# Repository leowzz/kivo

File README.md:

# Kivo

把实体按键变成电脑里的文字、快捷键和自动化动作。

[下载最新版本](https://github.com/leowzz/kivo/releases/latest) · [快速上手](#快速上手) · [刷入固件](#刷入固件) · [本地开发](#本地开发)

Kivo 包含两个独立的 Tauri 桌面入口：日常使用的 **Kivo APP**，以及配置产品、硬件和固件的 **Kivo Studio**。APP 从设备读取产品定义，负责按键动作；Studio 负责生成产品固件并检查 GPIO 电平。

## 能做什么

- **执行桌面动作**：按顺序组合文字粘贴、快捷键、等待、媒体控制，以及打开应用、网址、文件或文件夹。
- **配置触发方式**：为按下、松开、长按和双击分别配置动作，并调整长按、双击的判定时间。
- **配置产品硬件**：Studio 编辑按键布局、直连 GPIO、触点矩阵、功能开关和显示模块。
- **测试 GPIO 电平**：Studio 实时展示板卡允许使用的 GPIO 高低电平，支持 YD-ESP32-S3 和 YD-RP2040。
- **管理多台设备**：每台产品设备独立选择动作配置；相同产品版本的设备可以共享配置，也可以复制一份单独修改。
- **兼容旧版配置**：通用固件仍可使用包含布局、动作和多个 Hardware Profile 的 Device Profile。
- **功能开关门控**：Hardware Profile 可把一个 GPIO 开关绑定到若干按钮；开关断开时，这些按钮不会执行动作。
- **编辑按键动作**：APP 展示设备键盘，支持动作列表、自动保存、撤销和重做。
- **迁移与恢复**：导入旧版设备配置，备份和恢复产品设备的动作配置及其选择关系；仍兼容恢复旧版全量备份。

## 快速上手

1. 从 [Releases](https://github.com/leowzz/kivo/releases/latest) 下载 macOS 安装包或 Windows x64 安装程序。
2. 已刷入产品固件的设备直接连接 USB 即可。裸板或需要更换固件的设备，先按[刷入固件](#刷入固件)选择产品固件或通用固件。通过身份与协议校验后，Kivo 会自动登记设备。
3. 产品固件会直接提供按键布局和硬件定义。在 APP 的“我的键盘”中选中设备，再选择或新建动作配置。
4. 点击按键，为不同触发方式编辑动作。修改自动保存，提供撤销和重做；修改共享配置会影响所有正在使用它的设备，需要独立设置时先复制配置。
5. 改接线、布局或显示模块时，使用 Studio 修改产品定义并重新构建固件。
6. 通用固件仍可使用已有 Device Profile：通过“添加键盘”选择兼容配置，或从“数据与备份”导入旧配置。

产品设备会按 Product Version ID 选择已有或默认动作配置。通用固件设备在获得有效 Runtime Assignment 前不会执行动作；编辑中的 Device Profile 不会自动替换其他设备正在使用的配置。

动作库中的“打开应用”可选择应用、拖入应用或快捷方式，也可填写完整路径：macOS 支持 `.app`，Windows 支持 `.exe`、`.com` 和 `.lnk`。“打开网址”使用默认浏览器，支持 HTTP 和 HTTPS，未填写协议时自动使用 HTTPS。选择目标并保存后，这些动作会按配置顺序执行。

APP 的“设置 → 应用更新”和 Studio 的“应用更新”可手动检查新版。桌面应用也会在启动及重新回到前台时检查更新；发现新版后，点击“更新并重启”即可下载、验证并安装更新。更新应用前请先保存修改并完成设备操作。应用更新不会刷写设备固件。

“数据与备份”中的“备份设备行为”导出产品动作配置与设备选择关系，不包含固件、布局、接线、统计数据或旧版 Device Profile，不能当作整个工作区的全量备份。设备 Flash 的备份与恢复在 Studio 的工具台完成。

## 刷入固件

先区分两类固件：

- **产品固件**：由 Studio 根据 `products/<product-version-id>/product.yaml` 构建，内嵌布局和接线，APP 可自动识别。使用已有产品时应选择对应产品产物；构建与刷写步骤见[本地开发](#本地开发)和[固件](#固件)。
- **通用固件**：Release 中按板卡命名的文件，不含具体产品定义，需要在 APP 中分配兼容的旧版 Device Profile。不要把它当作某个产品的预配置固件。

从 [Releases](https://github.com/leowzz/kivo/releases/latest) 下载的通用固件命名如下：

| 板卡 | 选择这个文件 |
|---|---|
| YD-ESP32-S3 | `kivo-vX.Y.Z-esp32s3.bin` |
| YD-RP2040 | `kivo-vX.Y.Z-rp2040.uf2` |

### YD-RP2040：拖入文件管理器

1. 让板卡进入 BOOTSEL 模式：
   - 板卡尚未连接时，按住 **BOOT**，插入 USB；看到 `RPI-RP2` 磁盘后松开 **BOOT**。
   - 板卡已经连接时，按住 **BOOT**，短按一次 **RESET**，然后松开 **BOOT**。
2. 在 Finder 或文件资源管理器中打开 `RPI-RP2`。
3. 把 `kivo-vX.Y.Z-rp2040.uf2` 拖进磁盘。复制完成后磁盘会自动退出，板卡会运行 Kivo 固件。

### ESP32-S3：在浏览器中选择固件

ESP32-S3 的下载模式不会显示成磁盘。请使用 Chrome 或 Edge：

1. 下载 `kivo-vX.Y.Z-esp32s3.bin`，打开 Espressif 官方的 [ESP Tool](https://espressif.github.io/esptool-js/)。
2. 按住板卡的 **BOOT**，短按一次 **RESET/RST**，然后松开 **BOOT**。
3. 点击 **Connect**，选择刚出现的 ESP32-S3 串口。
4. 点击 **Add File**，地址填写 `0x0`，选择下载的 `.bin` 文件。
5. 点击 **Program**。完成后短按一次 **RESET/RST**，板卡会运行 Kivo 固件。

只使用上表中与板卡匹配的文件。刷写完成后保持 USB 连接，Kivo 会自动检测设备。

## 配置怎样组合

| 概念 | 负责什么 |
|---|---|
| Product Definition | Studio 编辑并嵌入固件的产品身份、布局和硬件定义 |
| Product Configuration Profile | APP 编辑的触发设置与动作；同一 Product Version ID 的设备可以共享，修改影响所有选用它的设备 |
| Device Profile | 通用固件的旧版兼容格式，包含布局、动作及一个或多个 Hardware Profile |
| Hardware Profile | 面向具体板卡的接线拓扑、输入绑定和去抖设置 |
| Device | 一台有稳定硬件序列号的实体控制器；USB 端口不是设备身份 |
| Runtime Assignment | 把一个 Device Profile 和兼容的 Hardware Profile 分配给一台 Device |
| Editor Profile | 当前正在界面中编辑的 Device Profile，不影响其他设备运行 |

功能开关属于 Hardware Profile 的输入源，不会出现在按键布局中。配置时只需选择开关 GPIO 和受影响的按钮。开关闭合时启用按钮；断开或 helper 尚未确认开关状态时屏蔽按钮。被屏蔽的按键不会计入动作统计，正在执行的动作会完整结束。

## 硬件产品命名

Kivo 实体产品使用 `<product-family>-<controller>-k<key-count>[-<capability>...]-r<hardware-revision>`
形式的 Product Version ID。产品能力变体和 PCB 修订彼此独立，软件发布版本、固件
版本、生产批次和单台设备序列号不进入该 ID。

仓库目前包含 WBRP-K18 的 r02、r03 产品定义：RP2040、18 个独立实体按键、显示屏，
以及可旋转、可按压的编码器。例如：

```text
kivo-workbench-rp-k18-disp-encp-r03
```

其中 `rp` 表示 RP2040，`k18` 不包含编码器按压，`encp` 表示编码器同时支持旋转和按压。
当前这两份产品定义不声明麦克风能力。产品 YAML 的存在不代表对应 PCB 已可投产；
[`hardware/workbench-r03/`](hardware/workbench-r03/README.md) 仍标记为未布线的设计草稿。
完整字段定义、token 顺序和升级规则见[产品版本 ID 命名规范](docs/product-version-id-naming.md)。

## 支持的控制器

| 板卡 | Controller Family | 运行时 USB | 固件环境 | 上传命令 |
|---|---|---|---|---|
| YD-ESP32-S3 | ESP32-S3 | `303a:4002` | `esp32s3` | `make upload-esp32s3` |
| YD-RP2040 | RP2040 | `2e8a:102e` | `rp2040` | `make upload-rp2040` |

YD-RP2040 的 UF2 bootloader USB 标识为 `2e8a:0003`。Kivo 会先校验 USB 身份，再通过 `HELLO` 协议确认板卡和固件；不受该 Board Profile 支持的 GPIO 会被拒绝。

YD-RP2040 的 Hardware Profile 支持两种地址为 `0x3C` 的 OLED：原有 SSD1306 128x32 模块占用 SDA/SCL 两个 GPIO；`sh1106-1.3-128x64-ec11` 模块使用 SH1106 128x64 屏，并带 EC11 旋转、EC11 按压、确认和返回，共占用七个 GPIO。OLED 和控制面板占用的 GPIO 不会再分配给按键输入。

## Codex 状态屏

启用 OLED 的设备会显示本机 Codex 任务的低干扰状态：汇总画面为 `CODEX <N> RUN`，需要操作时显示 `NEEDS INPUT` 或 `APPROVAL NEEDED`，响应生成后短暂显示 `RESPONSE READY`，数据源不可用时显示 `CODEX OFFLINE`。Codex 数据源异常不会停止 Kivo 的按键 Runtime。

状态屏使用任务身份、工作目录和状态/生命周期信号，不展示对话正文、推理、工具内容或最终回复。SSD1306 使用 `ssd1306_128x32` 面板和 128x32 渲染器；SH1106 使用 `sh1106_128x64` 面板和 128x64 渲染器。当前仓库的运行固件握手为 `HELLO 15`。两种屏均固定为 rotation 0，互不迁移。

带编码器的屏幕还提供 RunCat：按压编码器进入菜单，选择 `RUNCAT`，旋转编码器依次切换经典跑猫、兔子、柯基、飞鸟、奔马、恐龙、转子发动机、擒纵机构、双曲柄和 UFO 吸牛，共 10 套动画。素材来自 [Runner Gallery](https://github.com/runcat-dev/RunnerGallery)，保留各套完整的 5–24 帧循环；动画铺满屏幕高度，CPU 指标位于最右侧，不显示标题。动画选择会保存，按压编码器或返回键回到菜单，从 `LIVE VIEW` 恢复任务状态屏。电脑 CPU 使用率越高，动画播放越快；Kivo 未连接或 CPU 数据超过 3 秒未更新时显示 `CPU --`，动画以低速播放。此功能需要配套更新 Kivo 和运行固件。素材来源与许可证见 [assets/runcat/NOTICE.md](assets/runcat/NOTICE.md)。

带编码器的 r02 工作站使用产品固件：先运行 `make build-product PRODUCT=kivo-workbench-rp-k18-disp-encp-r02`，再用 `make upload-prod` 选择刚构建的 r02 固件。`make upload` 上传通用固件，不包含产品的屏幕和编码器接线；刷入后无法独立使用该模块的菜单。

刷入固件后仍需分别在实体 SSD1306 和 SH1106 上检查文字与状态切换，并在 SH1106 模块上检查旋钮方向、按压、确认和返回。自动测试和固件构建不能替代物理屏幕与输入验收。

两种控制器共享按键扫描、去抖、协议和运行状态机，各自保留 USB/HID 平台适配。多台 ESP32-S3 与 YD-RP2040 可以同时在线：产品设备使用各自选择的产品动作配置，通用固件设备使用各自的 Runtime Assignment。

## 本地开发

需要：

- Node.js `>=24.12.0 <25` 与 npm `>=11.0.0 <12`；`.nvmrc` 和
  `packageManager` 记录 CI 使用的参考版本
- Rust stable 和 Tauri 2 所需的系统构建依赖
- Python `3.13`、[`uv`](https://docs.astral.sh/uv/) 与 PlatformIO
- macOS 或 Windows；发行工作流构建 macOS universal DMG 和 Windows x64 NSIS 安装程序
- 使用 `make` 目标需要 GNU Make；Windows 还需可用的 Bash。Git for Windows 可以提供 Bash，但 GNU Make 需要单独安装

```bash
git clone https://github.com/leowzz/kivo.git
cd kivo
cp .env.example .env

nvm install
nvm use
uv sync
npm ci
make client
```

`.env` 会被有意忽略，且只包含 `version=vX.Y.Z`。它为本地固件构建和 `make release` 提供仓库版本。

### 两个桌面入口

| 命令 | 用途 |
|---|---|
| `make client` | 启动 Kivo APP，管理设备和按键动作 |
| `make studio` | 启动 Kivo Studio，编辑产品定义、构建固件、测试 GPIO |
| `make helper-build-app` | 单独打包 APP |
| `make helper-build-studio` | 单独打包 Studio |
| `make helper-build` | 打包两个入口 |
| `make test` | 前端、两个 Rust 入口、固件逻辑与构建流程验证 |

浏览器开发使用 `npm run dev` 和 `npm run dev:studio`，默认端口分别为 1420 和 1421。
APP 的 `/?preview` 仅在开发环境提供交互预览；真实串口和文件操作需要 Tauri。

Studio 使用独立的应用标识和配置目录，不会启动 APP 的设备运行服务。产品定义编辑可以与 APP 同时运行；GPIO 测试需要独占目标串口，测试前退出 APP 或其他串口工具。

安装版 Studio 首次使用时需要选择包含 `products/` 和固件源码的 Kivo 仓库；构建、备份和刷写还依赖本机的 `uv`、PlatformIO 等工具链，安装桌面包本身并不等于已配置固件开发环境。

已保存产品的 Capabilities 可直接修改；能力变化会同步更新产品 ID，保存时创建对应的新变体。
构建完成后，日志面板提供“复制输出路径”和“刷入固件”。后者直接使用本次构建文件，筛选匹配板卡的设备，校验文件后确认覆盖；未保存的修改需要先保存并重新构建。

### 工具台

Studio 的“工具台”集中提供刷新设备列表、备份固件、刷入固件文件和刷入测试固件四项操作，并可查看 GPIO 高低电平。

- **刷新设备列表**：重新枚举受支持的板卡，操作按序列号定位所选物理设备。
- **备份固件**：读取整片 Flash，RP2040 保存为 UF2，ESP32-S3 保存为 BIN；同时保存 `.backup.json` 校验记录。读取失败不会覆盖已有备份。
- **刷入固件文件**：选择 RP2040 UF2 或 ESP32-S3 完整 Flash / factory BIN，检查芯片、文件结构和 SHA-256 后确认刷写。支持恢复备份；若文件附带产品 `manifest.json`，额外校验清单和刷写后的产品、构建身份。ESP32-S3 写入地址固定为 `0x0`，拒绝仅含应用、应写入 `0x10000` 的 BIN。
- **刷入测试固件**：自动构建所选板卡的临时 I/O 固件，首次刷入前备份原固件，完成后开始采样。测试固件不含产品接线、按键动作、矩阵扫描或显示驱动；安全 GPIO 默认上拉输入，可切换浮空或下拉，串口断开时回到上拉输入。Studio 每次开始测试时也会先为临时固件启用上拉，兼容默认浮空的旧测试固件。

原固件备份位于 `output/firmware-backups/<board>/<device>/`，工具台显示具体路径。备份按设备持久保存，重复刷测试固件会复用原备份，不会把测试固件覆盖到原备份。测试完成后停止采样，点击“刷入固件文件”，文件选择器会默认定位到原备份。恢复成功后保留备份文件并结束此次临时测试记录。

每次采样完成后约 125 ms 再次读取。已有产品固件若支持 `GPIO_READ`，也可直接查看当前电平，但工具台不会修改它的引脚模式或运行拓扑。瞬时 HIGH / LOW 不等于连通性；悬空输入、矩阵扫描和通信引脚可能变化，应结合接线判断。

操作需要已配置的 Kivo 仓库、`uv` 和 PlatformIO 工具链。操作期间设备选择、工作区切换和窗口关闭被锁定；请勿拔线，并先退出 APP 或其他串口工具。设备留在引导模式时，可在当前视图直接重试，仍按原序列号定位设备。RP2040 自动进入与定位 BOOTSEL 沿用现有 macOS / Windows 上传工具。

备份文件是设备的完整 Flash 镜像，APP 动作配置仍使用 APP 的配置备份。`make build-io-test` 可单独构建两种测试固件，产物位于 `output/io-test/`；此命令不会操作硬件。

入口边界、目录职责和诊断协议见[架构说明](docs/architecture.md)。逐键学习已从界面、桌面协议和固件移除。

仓库的 `.envrc` 会加载 `.nvmrc` 中的精确 Node 版本。使用 direnv 时可以验证实际解析到的工具：

```bash
direnv allow
direnv exec . node --version
direnv exec . npm --version
```

预期分别输出 `v24.18.0` 和 `11.16.0`。

Windows PowerShell 不需要 direnv。安装 `.nvmrc` 中的版本后可以直接启动：

```powershell
nvm install 24.18.0
nvm use 24.18.0
npm install --global npm@11.16.0
Copy-Item .env.example .env
uv sync
npm ci
uv run python scripts/kill_helper.py
npm run tauri dev
```

本地环境只要落在上述兼容范围内即可，不要求与 CI 的参考版本完全一致。

`make release` 默认递增 patch；`make release V=vX.Y.Z` 可指定版本。脏工作树会被拒绝，跟踪的包版本会以 `chore: release vX.Y.Z` 提交，最后才创建带注释的 tag。

## 固件

分别构建两个通用固件目标（不内嵌产品定义）：

```bash
make build-esp32s3
make build-rp2040
```

分别上传；不要使用泛化的 `make upload`：

```bash
make upload-esp32s3
make upload-rp2040
```

产品固件可以在 Studio 中构建，也可以指定产品 YAML：

```bash
make build-product PRODUCT=products/kivo-workbench-rp-k18-disp-encp-r03/product.yaml
```

产物写入 `output/products/<product-version-id>/<build-id>/`，其中包含固件、产品定义和 `manifest.json`。刷写已有产品产物时使用：

```bash
make upload-prod
```

命令会先选择已连接的设备，再扫描与板卡匹配的产品固件；确认后完成刷写，并用固件内嵌的 Product Version ID 和 Build ID 校验启动协议。需要固定设备或固件时可以直接指定：

```bash
make upload-prod SERIAL=E0C9125B0D9B \
  FIRMWARE=output/products/<product-version-id>/<build-id>/firmware.uf2
```

`FIRMWARE` 只能指向 `output/products/` 下与目标板卡匹配的 `.uf2`（RP2040）或 `.bin`（ESP32-S3）产品产物；未指定时会在终端选择器中列出全部可用版本。

当同时连接多块同型号板卡时，用稳定硬件序列号指定目标：

```bash
make upload-esp32s3 SERIAL=ABCDEF123456
make upload-rp2040 SERIAL=E0C9125B0D9B
```

监控固件的 USB CDC 串口（默认 `115200` 波特率）：

```bash
make monitor                 # 默认选择 RP2040
make monitor-rp2040
make monitor-esp32s3
```

未传 `SERIAL` 时会打开设备选择器；也可以直接指定设备和波特率：

```bash
make monitor-rp2040 SERIAL=E0C9125B0D9B
make monitor-esp32s3 SERIAL=ABCDEF123456 BAUD=921600
```

监控命令会先停止可能占用串口的 Kivo helper。按 `Ctrl+C` 退出监控。

### BLE RSSI 实验

ESP32-S3 的独立实验固件放在 [firmware/demos/ble-rssi](firmware/demos/ble-rssi/README.md)，支持手机系统蓝牙配对后读取连接 RSSI，以及扫描指定设备的 BLE 广播。电脑端 [host/ble_rssi](host/ble_rssi/README.md) 提供实时曲线、位置标记、历史保存与 CSV 导出。

实测数据和离开、回来阈值的适用范围见[实验记录](docs/research/ble-rssi-presence.md)。当前只采集信号，尚未接入屏幕控制。

## 测试与构建

```bash
make test
make helper-build
```

`make test` 会运行发布脚本测试、Python 上传/选择测试、PlatformIO native 测试、Rust 测试与 Clippy、前端测试和生产构建。`make helper-build` 会连续构建 Kivo 和 Kivo Product Studio 两套包：macOS 生成应用包，Windows 生成对应的 NSIS 安装程序。Windows CI 也会在每次 pull request 中验证两套 NSIS 安装程序。

Tag 发布会使用 GitHub Secret `TAURI_SIGNING_PRIVATE_KEY` 签名桌面更新包，并在 Windows x64 和 macOS universal 产物齐备后生成 `latest.json`（APP）及 `latest-studio.json`（Studio）。两个入口分别读取自己的清单。签名公钥保存在 Tauri 配置中；私钥需安全备份，不能提交到仓库。普通本地构建不生成签名更新包；需要验证更新包时，设置 `TAURI_SIGNING_PRIVATE_KEY` 并额外使用 `--config src-tauri/tauri.updater.conf.json`。首次支持应用内更新的版本仍需手动安装，之后即可通过应用内更新升级。

## 项目结构

```text
src/app/             APP 入口、设备管理、动作编辑、设置与备份
src/studio/          Studio 入口、产品定义编辑、固件构建与 GPIO 测试
src/shared/          两个前端入口共享的领域类型和基础样式
src-tauri/src/app/   APP 启动、运行服务装配与 IPC 命令
src-tauri/src/studio.rs  Studio 启动、产品仓库和构建命令
src-tauri/src/studio/    独立串口诊断会话
firmware/src/        固件入口与 ESP32-S3、RP2040 平台适配
firmware/demos/      独立实验固件，各自维护 PlatformIO 配置
host/ble_rssi/       BLE RSSI 采集服务与网页静态资源
lib/gpio_trigger/    板卡无关的输入拓扑、去抖与协议状态机
models/prod/         随应用发布的旧版 Device Profile
products/            Studio 管理的产品定义
hardware/            PCB、接线与硬件设计资料（完成状态见各目录说明）
scripts/             固件选择、上传与运行时验证工具
test/                Python、PlatformIO 与发布流程测试
docs/                硬件改造、兼容性与设计记录
```

领域术语以 [`CONTEXT.md`](CONTEXT.md) 为准，实体产品版本命名见
[`docs/product-version-id-naming.md`](docs/product-version-id-naming.md)。电话硬件改造和
电气安全要求见 [`docs/telephone-usb-voice-terminal-mod-guide.md`](docs/telephone-usb-voice-terminal-mod-guide.md)；
改造设备必须彻底隔离原 PSTN 电话线路。

## 平台状态

Kivo 支持 macOS 和 Windows 10/11 x64。Windows 使用原生 Unicode 剪贴板、系统托盘、COM/PnP 设备发现、按硬件身份锁定的 ESP32-S3/RP2040 上传流程，以及 x64 NSIS 安装程序。Windows 安装包目前未做代码签名，首次运行时可能显示系统信誉提示。

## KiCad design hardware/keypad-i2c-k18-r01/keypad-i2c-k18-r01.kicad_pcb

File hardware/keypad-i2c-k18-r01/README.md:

# Standalone 18-Key I2C PCB r01

Open `keypad-i2c-k18-r01.kicad_pro` in KiCad 10. This independent design is a
**routed 124 x 76 mm keyboard PCB**, with six columns and three rows of MX
hot-swap switches at 19.05 mm pitch. It connects to an external ESP32-S3 using
four individual Dupont wires. The older Workbench designs are separate projects.

The board has 43 electrical components: 18 sockets, 18 diodes, one MCP23017,
one four-position female connector, two capacitors and three resistors.
There is no controller carrier, display connector, USB port, regulator,
expansion connector, BOOT/RESET button, or board-to-board panel connection.
The four mounting holes are mechanical only.

## J1 Wiring

J1 is a **1x4 vertical female socket, 2.54 mm pitch**, for standard 0.64 mm
square male pins. Its four plated PCB holes have 1.0 mm drills. Purchase the
ordinary solder-tail female strip, not a 2.50 mm JST XH connector.

Viewed from the component/key side, with the chip and connector at the top,
pin 1 is the **leftmost square pad**. The signals run left to right:

| J1 pin | Signal | External YD ESP32-S3 connection |
| --- | --- | --- |
| 1 | GND | GND, manufacturer P1 pin 22 |
| 2 | 3V3 | 3V3, manufacturer P1 pin 1 or 2 |
| 3 | SDA | GPIO13, manufacturer P1 pin 19 |
| 4 | SCL | GPIO14, manufacturer P1 pin 20 |

Use **four separate male-to-female Dupont wires**: male ends into J1, female
ends onto the ESP32-S3's installed male header. The pitch matches the S3
header, but these four signals are not four consecutive S3 pins. Do not
plug the whole block across an arbitrary run of four GPIOs. Follow the
actual core board's printed signal labels; P1 numbering above applies to
the repository's YD ESP32-S3 reference board.

From the PCB underside, the square pad is at the right and the readable
silkscreen runs **SCL, SDA, 3V3, GND** from left to right. Each signal label
is aligned to its own pad. `interconnect.csv` records the same connections.

Power this PCB from the S3's **3.3 V**, never 5 V. No voltage regulator or
level shifting is present. Keep the four wires short, initially about
100-150 mm; start I2C at 100 kHz. Validate rise time before increasing to
400 kHz. R1/R2 provide 2.2 kohm pull-ups to 3.3 V. Account for any additional
pull-ups elsewhere on a shared bus; all pull-ups must go to 3.3 V.

## Keys And I2C Chip

U1 is **MCP23017-E/SO**, SOIC-28 wide with 1.27 mm exposed leads and no
underside thermal pad. Its fixed 7-bit I2C address is **0x20**, with A0-A2
tied to GND. Use this I2C part and SOIC package; MCP23S17 is SPI and uses a
different interface. R3 holds RESET high. C2 is the 100 nF local decoupler,
with short, via-free connections to U1 pins 9 and 10; C1 is 10 uF at J1.

| Function | Ports |
| --- | --- |
| Rows, rear to front | GPA5, GPA6, GPA7 |
| Columns, left to right | GPB0, GPB1, GPB2, GPB3, GPB4, GPB5 |
| Unused GPIO | GPA0-GPA4, GPB6, GPB7 |
| Unconnected interrupt outputs | INTA, INTB |

K1-K6 are the rear row, K7-K12 the middle row and K13-K18 the front row,
all numbered from the key side. D1 belongs to K1, and so on. Each path is
column -> switch -> diode anode -> diode cathode -> row. The stripe on the
**1N4148W SOD-123** diode faces its cathode pad 1, connected to the row.
The SOD-123 footprint is not interchangeable with SOD-323.

This is an I2C peripheral, not a USB keyboard by itself. Existing direct-GPIO
Kivo firmware cannot scan it unchanged. The hardware work does not add an
MCP23017 firmware backend. A scanner must preload GPA5-GPA7 output latches
HIGH, enable the row outputs, select one LOW at a time, and read GPB0-GPB5
with internal pull-ups. Debounce and simultaneous-key handling remain
firmware responsibilities. Set unused ports to defined states, for example
outputs LOW. Current MCP23017 silicon specifies GPA7 and GPB7 as output-only;
GPA7 is correctly used as a row output and GPB7 is unused here.

## Mechanical And Hand Assembly

- PCB: 124 x 76 mm, two copper layers, 1.6 mm FR-4, nominal 1 oz copper.
- Key centers: X = 14.375 + column * 19.05 mm; Y = 26 + row * 19.05 mm,
  with zero-based column/row indices. `key-coordinates.csv` lists all 18.
- Four 3.4 mm NPTH M3 mounting holes: (4,4), (120,4), (4,72), (120,72) mm.
  Coordinates are from the rear-left PCB corner in the front view.
- Screw-head copper keepouts have 3 mm radius. Use heads no larger than
  5.6 mm and no large washers; check enclosure bosses and tool access.
- U1, J1, R1-R3 and C1-C2 are on the front. All 18 hot-swap sockets and
  diodes are on the back. Keep clearance below sockets and diode bodies.
- Switches need a suitable switch plate and socket support during insertion.
  The previous enclosure is not automatically compatible with this outline.

R1-R3 and C1-C2 use **0402 imperial (1005 metric, 1.0 x 0.5 mm)** bodies
with elongated hand-solder pads. R1/R2 are 2.2 kohm, R3 is 10 kohm; use 1%
resistors rated at least 1/16 W. C1 is 10 uF / 10 V / X5R, and C2 is
100 nF / 16 V / X7R. MLCC capacitance falls under DC bias; C1 is nominal
bulk bypass and C2 remains the short local decoupler. Check the selected
capacitor's 3.3 V bias curve when sourcing it. Do not substitute metric
0402 (imperial 01005) parts or the previous 0805 parts on these pads.
The 18 key positions and 124 x 76 mm outline are unchanged by this package
update; the MX key pitch determines the main board area.

Solder U1 first with flux, then the 0402 resistors/capacitors, SOD-123 diodes,
hot-swap sockets and J1. All are intended for soldering-iron assembly, with
no hot-air station or bare MCU assembly. Inspect U1 bridges and diode
polarity, then check 3V3-to-GND resistance and all four cable connections
before applying power. Actual socket, keycap, header and enclosure fit still
need physical validation; DRC and rendered component models cannot establish
that fit.

## Outputs And Verification

`verification.md` records the checks. The schematic, PCB, project, local
footprints, hot-swap STEP model, BOM and coordinate/wiring tables are the
editable design. KiCad's normal libraries supply the remaining footprints
and 3D models. The checked-in PCB is the routed master.

Generated files are in `output/hardware/keypad-i2c-k18-r01/` from the repository
root: top/bottom PNG previews, schematic SVG/PNG, ERC/DRC reports, drill report,
and `keypad-i2c-k18-r01-gerbers.zip`. The ZIP contains the nine manufacturing
Gerber layers, job file and separate plated/non-plated drill files. There is
one rectangular board, with no breakaway tabs or V-scoring. Specify tented
vias. Confirm actual parts and plate/enclosure fit before ordering.

## Reproduction

Generate into a fresh directory to preserve manual KiCad edits. The schematic
generator reuses the original S3 design's symbols and the repository's
schematic formatting helpers; the finished KiCad directory is self-contained
apart from the installed standard KiCad libraries.

```sh
uv run --script scripts/hardware/generate_keypad_i2c.py --output /tmp/keypad-i2c-review
/Applications/KiCad/KiCad.app/Contents/Frameworks/Python.framework/Versions/3.9/bin/python3.9 scripts/hardware/pcb_keypad_i2c.py place /tmp/keypad-i2c-review/placement.json /tmp/keypad-i2c-review/placement.kicad_pcb
java -jar /path/to/freerouting-1.9.0.jar -de /tmp/keypad-i2c-review/placement.dsn -do /tmp/keypad-i2c-review/routed.ses -mp 10 -mt 1 -da
/Applications/KiCad/KiCad.app/Contents/Frameworks/Python.framework/Versions/3.9/bin/python3.9 scripts/hardware/pcb_keypad_i2c.py finish /tmp/keypad-i2c-review/placement.json /tmp/keypad-i2c-review/placement.kicad_pcb --session /tmp/keypad-i2c-review/routed.ses --output /tmp/keypad-i2c-review/keypad-i2c-k18-r01.kicad_pcb
/Applications/KiCad/KiCad.app/Contents/MacOS/kicad-cli sch export netlist --format kicadxml -o /tmp/keypad-i2c-review/netlist.xml /tmp/keypad-i2c-review/keypad-i2c-k18-r01.kicad_sch
/Applications/KiCad/KiCad.app/Contents/Frameworks/Python.framework/Versions/3.9/bin/python3.9 scripts/hardware/pcb_keypad_i2c.py verify /tmp/keypad-i2c-review/placement.json /tmp/keypad-i2c-review/keypad-i2c-k18-r01.kicad_pcb --netlist /tmp/keypad-i2c-review/netlist.xml
```

Run KiCad ERC and DRC with warnings enabled after regeneration or edits.
Freerouting 1.9 needs a graphical Java environment even when invoked with
file arguments. Routing scripts do not replace electrical or assembly review.

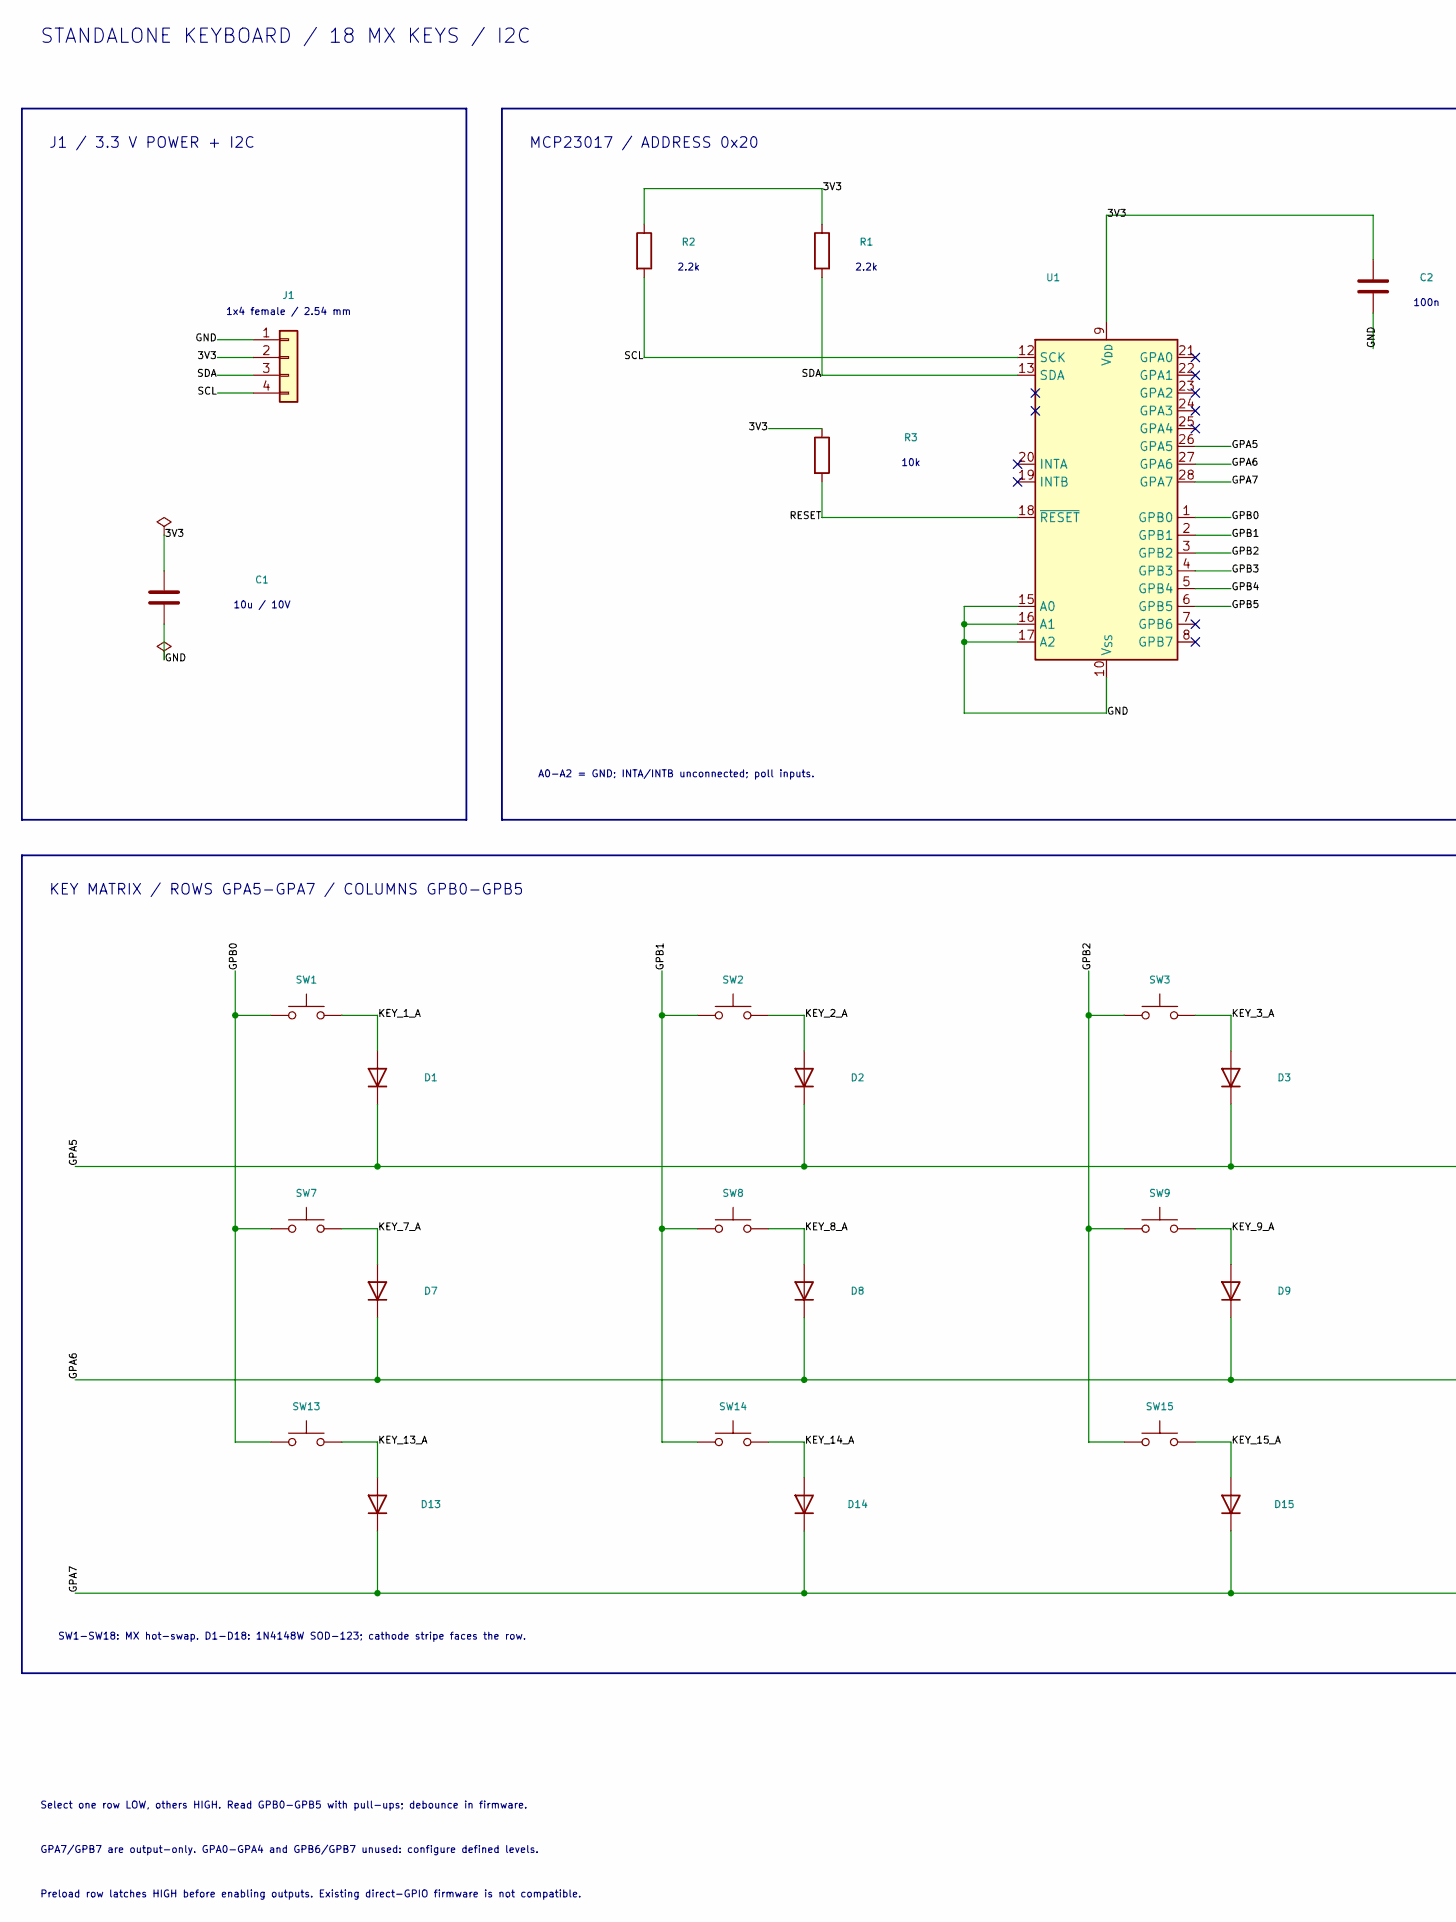
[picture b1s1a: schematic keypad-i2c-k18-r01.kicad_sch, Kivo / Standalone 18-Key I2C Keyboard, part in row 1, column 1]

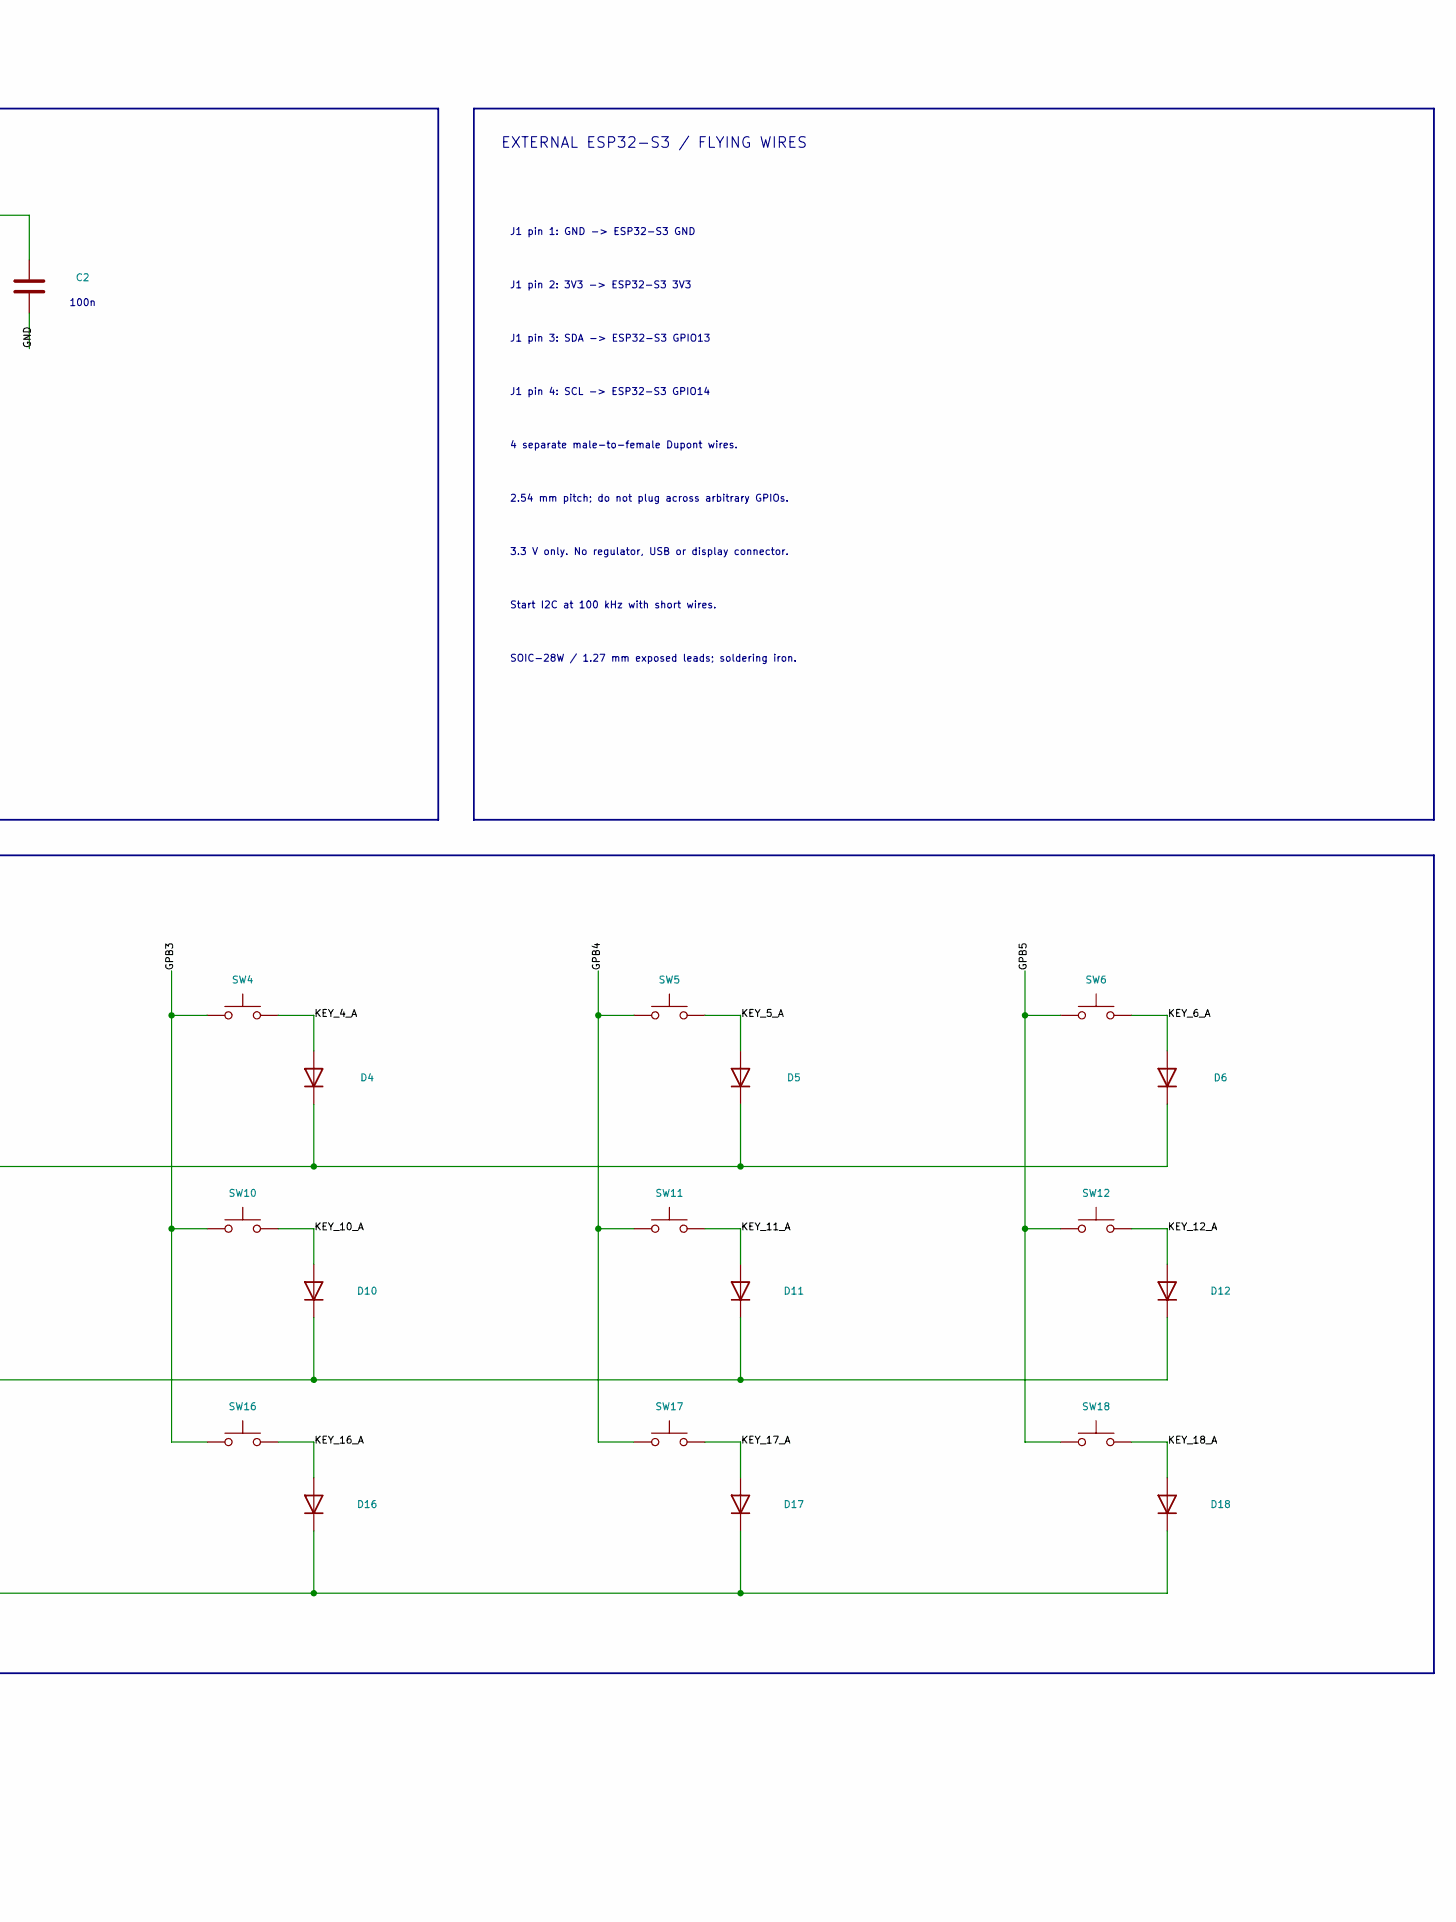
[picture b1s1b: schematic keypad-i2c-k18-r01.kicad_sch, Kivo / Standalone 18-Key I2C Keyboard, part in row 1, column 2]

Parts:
C1: 10u 10V X5R; C_0402_1005Metric_Pad0.74x0.62mm_HandSolder
C2: 100n 16V X7R / U1; C_0402_1005Metric_Pad0.74x0.62mm_HandSolder
D1, D2, D3, D4, D5, D6, D7, D8, D9, D10, D11, D12, D13, D14, D15, D16, D17, D18: 1N4148W / K TO ROW; D_SOD-123
J1: I2C / 3V3 / 1x4 FEMALE / 2.54mm; PinSocket_1x04_P2.54mm_Vertical
R1, R2: 2.2k I2C PULLUP; R_0402_1005Metric_Pad0.72x0.64mm_HandSolder
R3: 10k U1 RESET PULLUP; R_0402_1005Metric_Pad0.72x0.64mm_HandSolder
SW1: KEY_1 MX HOTSWAP; keyswitch_cherrymx_hotswap_1u
SW2: KEY_2 MX HOTSWAP; keyswitch_cherrymx_hotswap_1u
SW3: KEY_3 MX HOTSWAP; keyswitch_cherrymx_hotswap_1u
SW4: KEY_4 MX HOTSWAP; keyswitch_cherrymx_hotswap_1u
SW5: KEY_5 MX HOTSWAP; keyswitch_cherrymx_hotswap_1u
SW6: KEY_6 MX HOTSWAP; keyswitch_cherrymx_hotswap_1u
SW7: KEY_7 MX HOTSWAP; keyswitch_cherrymx_hotswap_1u
SW8: KEY_8 MX HOTSWAP; keyswitch_cherrymx_hotswap_1u
SW9: KEY_9 MX HOTSWAP; keyswitch_cherrymx_hotswap_1u
SW10: KEY_10 MX HOTSWAP; keyswitch_cherrymx_hotswap_1u
SW11: KEY_11 MX HOTSWAP; keyswitch_cherrymx_hotswap_1u
SW12: KEY_12 MX HOTSWAP; keyswitch_cherrymx_hotswap_1u
SW13: KEY_13 MX HOTSWAP; keyswitch_cherrymx_hotswap_1u
SW14: KEY_14 MX HOTSWAP; keyswitch_cherrymx_hotswap_1u
SW15: KEY_15 MX HOTSWAP; keyswitch_cherrymx_hotswap_1u
SW16: KEY_16 MX HOTSWAP; keyswitch_cherrymx_hotswap_1u
SW17: KEY_17 MX HOTSWAP; keyswitch_cherrymx_hotswap_1u
SW18: KEY_18 MX HOTSWAP; keyswitch_cherrymx_hotswap_1u
U1: MCP23017-E/SO / 0x20; SOIC-28W_7.5x17.9mm_P1.27mm

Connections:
/3V3: C1.1, C2.1, J1.2, R1.1, R2.1, R3.1, U1.9 (V_{DD})
/GND: C1.2, C2.2, J1.1, U1.10 (V_{SS}), U1.15 (A0), U1.16 (A1), U1.17 (A2)
/GPA5: D1.1 (K), D2.1 (K), D3.1 (K), D4.1 (K), D5.1 (K), D6.1 (K), U1.26 (GPA5)
/GPA6: D7.1 (K), D8.1 (K), D9.1 (K), D10.1 (K), D11.1 (K), D12.1 (K), U1.27 (GPA6)
/GPA7: D13.1 (K), D14.1 (K), D15.1 (K), D16.1 (K), D17.1 (K), D18.1 (K), U1.28 (GPA7)
/GPB0: SW1.1, SW7.1, SW13.1, U1.1 (GPB0)
/GPB1: SW2.1, SW8.1, SW14.1, U1.2 (GPB1)
/GPB2: SW3.1, SW9.1, SW15.1, U1.3 (GPB2)
/GPB3: SW4.1, SW10.1, SW16.1, U1.4 (GPB3)
/GPB4: SW5.1, SW11.1, SW17.1, U1.5 (GPB4)
/GPB5: SW6.1, SW12.1, SW18.1, U1.6 (GPB5)
/KEY_1_A: D1.2 (A), SW1.2
/KEY_2_A: D2.2 (A), SW2.2
/KEY_3_A: D3.2 (A), SW3.2
/KEY_4_A: D4.2 (A), SW4.2
/KEY_5_A: D5.2 (A), SW5.2
/KEY_6_A: D6.2 (A), SW6.2
/KEY_7_A: D7.2 (A), SW7.2
/KEY_8_A: D8.2 (A), SW8.2
/KEY_9_A: D9.2 (A), SW9.2
/KEY_10_A: D10.2 (A), SW10.2
/KEY_11_A: D11.2 (A), SW11.2
/KEY_12_A: D12.2 (A), SW12.2
/KEY_13_A: D13.2 (A), SW13.2
/KEY_14_A: D14.2 (A), SW14.2
/KEY_15_A: D15.2 (A), SW15.2
/KEY_16_A: D16.2 (A), SW16.2
/KEY_17_A: D17.2 (A), SW17.2
/KEY_18_A: D18.2 (A), SW18.2
/RESET: R3.2, U1.18 (~RESET)
/SCL: J1.4, R2.2, U1.12 (SCK)
/SDA: J1.3, R1.2, U1.13 (SDA)

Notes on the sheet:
STANDALONE KEYBOARD / 18 MX KEYS / I2C
J1 / 3.3 V POWER + I2C
MCP23017 / ADDRESS 0x20
EXTERNAL ESP32-S3 / FLYING WIRES
1x4 female / 2.54 mm
10u / 10V
2.2k
100n
10k
A0-A2 = GND; INTA/INTB unconnected; poll inputs.
J1 pin 1: GND -> ESP32-S3 GND
J1 pin 2: 3V3 -> ESP32-S3 3V3
J1 pin 3: SDA -> ESP32-S3 GPIO13
J1 pin 4: SCL -> ESP32-S3 GPIO14
4 separate male-to-female Dupont wires.
2.54 mm pitch; do not plug across arbitrary GPIOs.
3.3 V only. No regulator, USB or display connector.
Start I2C at 100 kHz with short wires.
SOIC-28W / 1.27 mm exposed leads; soldering iron.
KEY MATRIX / ROWS GPA5-GPA7 / COLUMNS GPB0-GPB5
SW1-SW18: MX hot-swap. D1-D18: 1N4148W SOD-123; cathode stripe faces the row.
Select one row LOW, others HIGH. Read GPB0-GPB5 with pull-ups; debounce in firmware.
GPA7/GPB7 are output-only. GPA0-GPA4 and GPB6/GPB7 unused: configure defined levels.
Preload row latches HIGH before enabling outputs. Existing direct-GPIO firmware is not compatible.

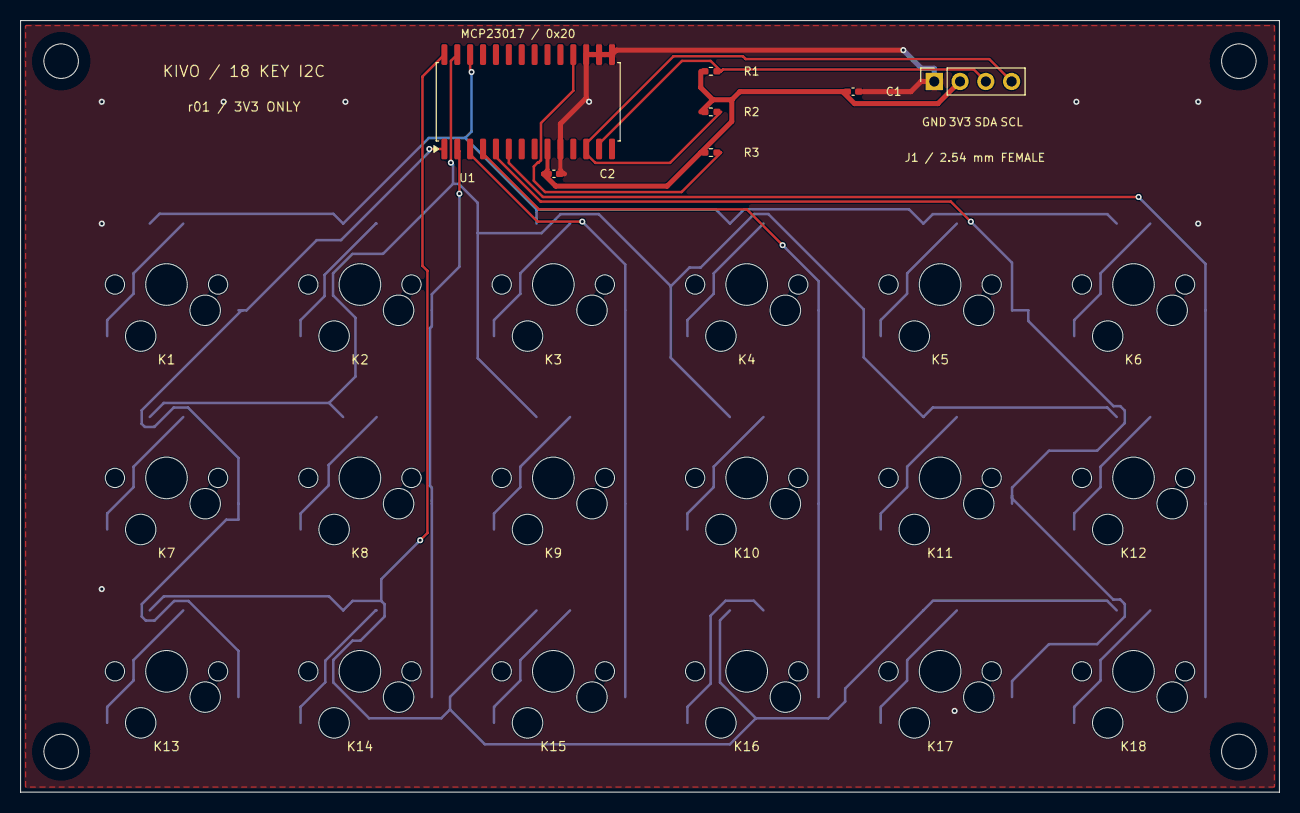
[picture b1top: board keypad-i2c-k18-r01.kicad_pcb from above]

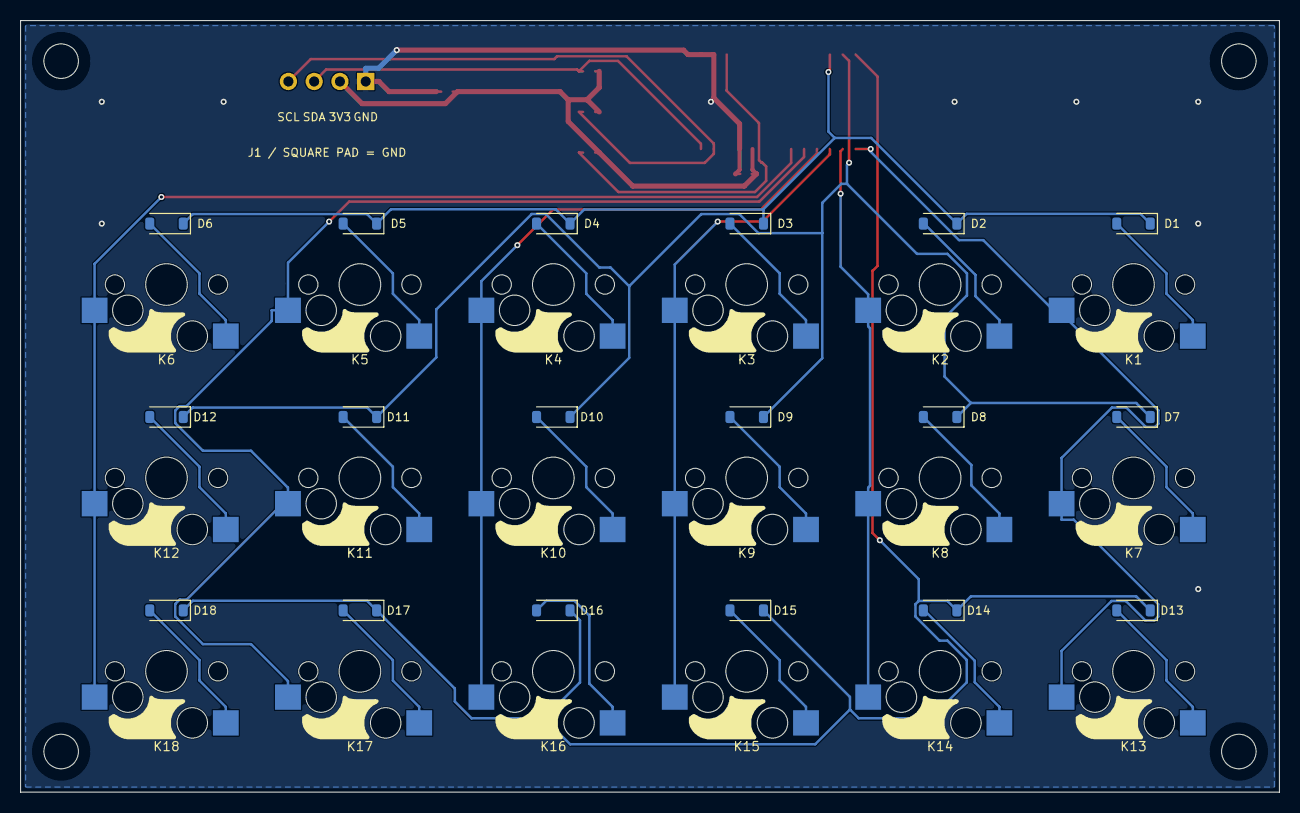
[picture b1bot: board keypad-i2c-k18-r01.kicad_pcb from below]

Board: 2 copper layers, 124.0 x 76.0 mm, 47 parts (36 on the bottom side), 32 nets.

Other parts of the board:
H1, H2, H3, H4: M3 head <=5.6mm; MountingHole_M3_5.6mm_Head

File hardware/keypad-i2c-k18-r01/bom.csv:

Reference,Value,Footprint,MPN
C1,10u 10V X5R,Capacitor_SMD:C_0402_1005Metric_Pad0.74x0.62mm_HandSolder,
C2,100n 16V X7R / U1,Capacitor_SMD:C_0402_1005Metric_Pad0.74x0.62mm_HandSolder,
R1,2.2k I2C PULLUP,Resistor_SMD:R_0402_1005Metric_Pad0.72x0.64mm_HandSolder,
R2,2.2k I2C PULLUP,Resistor_SMD:R_0402_1005Metric_Pad0.72x0.64mm_HandSolder,
R3,10k U1 RESET PULLUP,Resistor_SMD:R_0402_1005Metric_Pad0.72x0.64mm_HandSolder,
U1,MCP23017-E/SO / 0x20,Package_SO:SOIC-28W_7.5x17.9mm_P1.27mm,MCP23017-E/SO
J1,I2C / 3V3 / 1x4 FEMALE / 2.54mm,Connector_PinSocket_2.54mm:PinSocket_1x04_P2.54mm_Vertical,
SW1,KEY_1 MX HOTSWAP,Workbench:keyswitch_cherrymx_hotswap_1u,
D1,1N4148W / K TO ROW,Diode_SMD:D_SOD-123,1N4148W
SW2,KEY_2 MX HOTSWAP,Workbench:keyswitch_cherrymx_hotswap_1u,
D2,1N4148W / K TO ROW,Diode_SMD:D_SOD-123,1N4148W
SW3,KEY_3 MX HOTSWAP,Workbench:keyswitch_cherrymx_hotswap_1u,
D3,1N4148W / K TO ROW,Diode_SMD:D_SOD-123,1N4148W
SW4,KEY_4 MX HOTSWAP,Workbench:keyswitch_cherrymx_hotswap_1u,
D4,1N4148W / K TO ROW,Diode_SMD:D_SOD-123,1N4148W
SW5,KEY_5 MX HOTSWAP,Workbench:keyswitch_cherrymx_hotswap_1u,
D5,1N4148W / K TO ROW,Diode_SMD:D_SOD-123,1N4148W
SW6,KEY_6 MX HOTSWAP,Workbench:keyswitch_cherrymx_hotswap_1u,
D6,1N4148W / K TO ROW,Diode_SMD:D_SOD-123,1N4148W
SW7,KEY_7 MX HOTSWAP,Workbench:keyswitch_cherrymx_hotswap_1u,
D7,1N4148W / K TO ROW,Diode_SMD:D_SOD-123,1N4148W
SW8,KEY_8 MX HOTSWAP,Workbench:keyswitch_cherrymx_hotswap_1u,
D8,1N4148W / K TO ROW,Diode_SMD:D_SOD-123,1N4148W
SW9,KEY_9 MX HOTSWAP,Workbench:keyswitch_cherrymx_hotswap_1u,
D9,1N4148W / K TO ROW,Diode_SMD:D_SOD-123,1N4148W
SW10,KEY_10 MX HOTSWAP,Workbench:keyswitch_cherrymx_hotswap_1u,
D10,1N4148W / K TO ROW,Diode_SMD:D_SOD-123,1N4148W
SW11,KEY_11 MX HOTSWAP,Workbench:keyswitch_cherrymx_hotswap_1u,
D11,1N4148W / K TO ROW,Diode_SMD:D_SOD-123,1N4148W
SW12,KEY_12 MX HOTSWAP,Workbench:keyswitch_cherrymx_hotswap_1u,
D12,1N4148W / K TO ROW,Diode_SMD:D_SOD-123,1N4148W
SW13,KEY_13 MX HOTSWAP,Workbench:keyswitch_cherrymx_hotswap_1u,
D13,1N4148W / K TO ROW,Diode_SMD:D_SOD-123,1N4148W
SW14,KEY_14 MX HOTSWAP,Workbench:keyswitch_cherrymx_hotswap_1u,
D14,1N4148W / K TO ROW,Diode_SMD:D_SOD-123,1N4148W
SW15,KEY_15 MX HOTSWAP,Workbench:keyswitch_cherrymx_hotswap_1u,
D15,1N4148W / K TO ROW,Diode_SMD:D_SOD-123,1N4148W
SW16,KEY_16 MX HOTSWAP,Workbench:keyswitch_cherrymx_hotswap_1u,
D16,1N4148W / K TO ROW,Diode_SMD:D_SOD-123,1N4148W
SW17,KEY_17 MX HOTSWAP,Workbench:keyswitch_cherrymx_hotswap_1u,
D17,1N4148W / K TO ROW,Diode_SMD:D_SOD-123,1N4148W
SW18,KEY_18 MX HOTSWAP,Workbench:keyswitch_cherrymx_hotswap_1u,
D18,1N4148W / K TO ROW,Diode_SMD:D_SOD-123,1N4148W

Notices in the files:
hardware/workbench-s3-r01/README.md:
draft with its MIT license in `licenses/`.
